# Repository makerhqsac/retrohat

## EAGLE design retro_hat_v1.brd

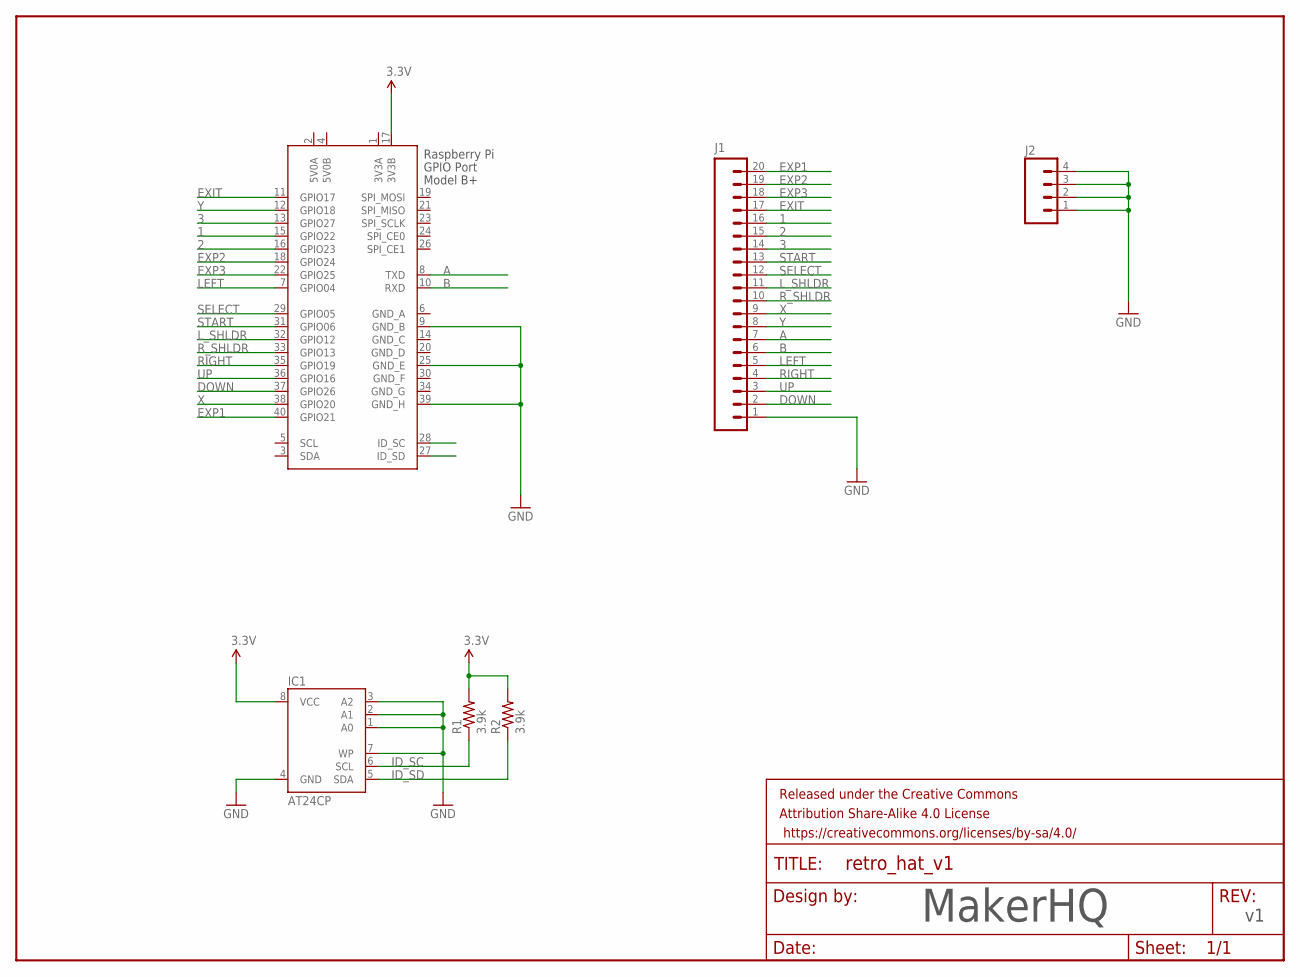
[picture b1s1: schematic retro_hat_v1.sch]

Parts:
FRAME1: FRAME-LETTERNO_PACKAGE; DUMMY
IC1: AT24CP; DIL08
J1: M20; 1X20
J2: M04PTH; 1X04
R1, R2: 3.9k; AXIAL-0.4
X1: RASPI_BOARD_B+#_HD; RASPI_BOARD_B+HAT_DF

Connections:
1: J1.16, X1.15 (GPIO22)
2: J1.15, X1.16 (GPIO23)
3: J1.14, X1.13 (GPIO27)
3.3V: IC1.8 (VCC), R1.P$2 (2), R2.P$2 (2), X1.17 (3V3B)
3V3A: X1.1 (3V3A)
5V0A: X1.2 (5V0A)
5V0B: X1.4 (5V0B)
A: J1.7, X1.8 (TXD)
B: J1.6, X1.10 (RXD)
DOWN: J1.2, X1.37 (GPIO26)
EXIT: J1.17, X1.11 (GPIO17)
EXP1: J1.20, X1.40 (GPIO21)
EXP2: J1.19, X1.18 (GPIO24)
EXP3: J1.18, X1.22 (GPIO25)
GND: IC1.1 (A0), IC1.2 (A1), IC1.3 (A2), IC1.4 (GND), IC1.7 (WP), J1.1, J2.1, J2.2, J2.3, J2.4, X1.9 (GND_B), X1.25 (GND_E), X1.39 (GND_H)
GND_A: X1.6 (GND_A)
GND_C: X1.14 (GND_C)
GND_D: X1.20 (GND_D)
GND_F: X1.30 (GND_F)
GND_G: X1.34 (GND_G)
ID_SC: IC1.6 (SCL), R1.P$1 (1), X1.28 (ID_SC)
ID_SD: IC1.5 (SDA), R2.P$1 (1), X1.27 (ID_SD)
LEFT: J1.5, X1.7 (GPIO04)
L_SHLDR: J1.11, X1.32 (GPIO12)
RIGHT: J1.4, X1.35 (GPIO19)
R_SHLDR: J1.10, X1.33 (GPIO13)
SELECT: J1.12, X1.29 (GPIO05)
START: J1.13, X1.31 (GPIO06)
UP: J1.3, X1.36 (GPIO16)
X: J1.9, X1.38 (GPIO20)
Y: J1.8, X1.12 (GPIO18)

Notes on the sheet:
MakerHQ

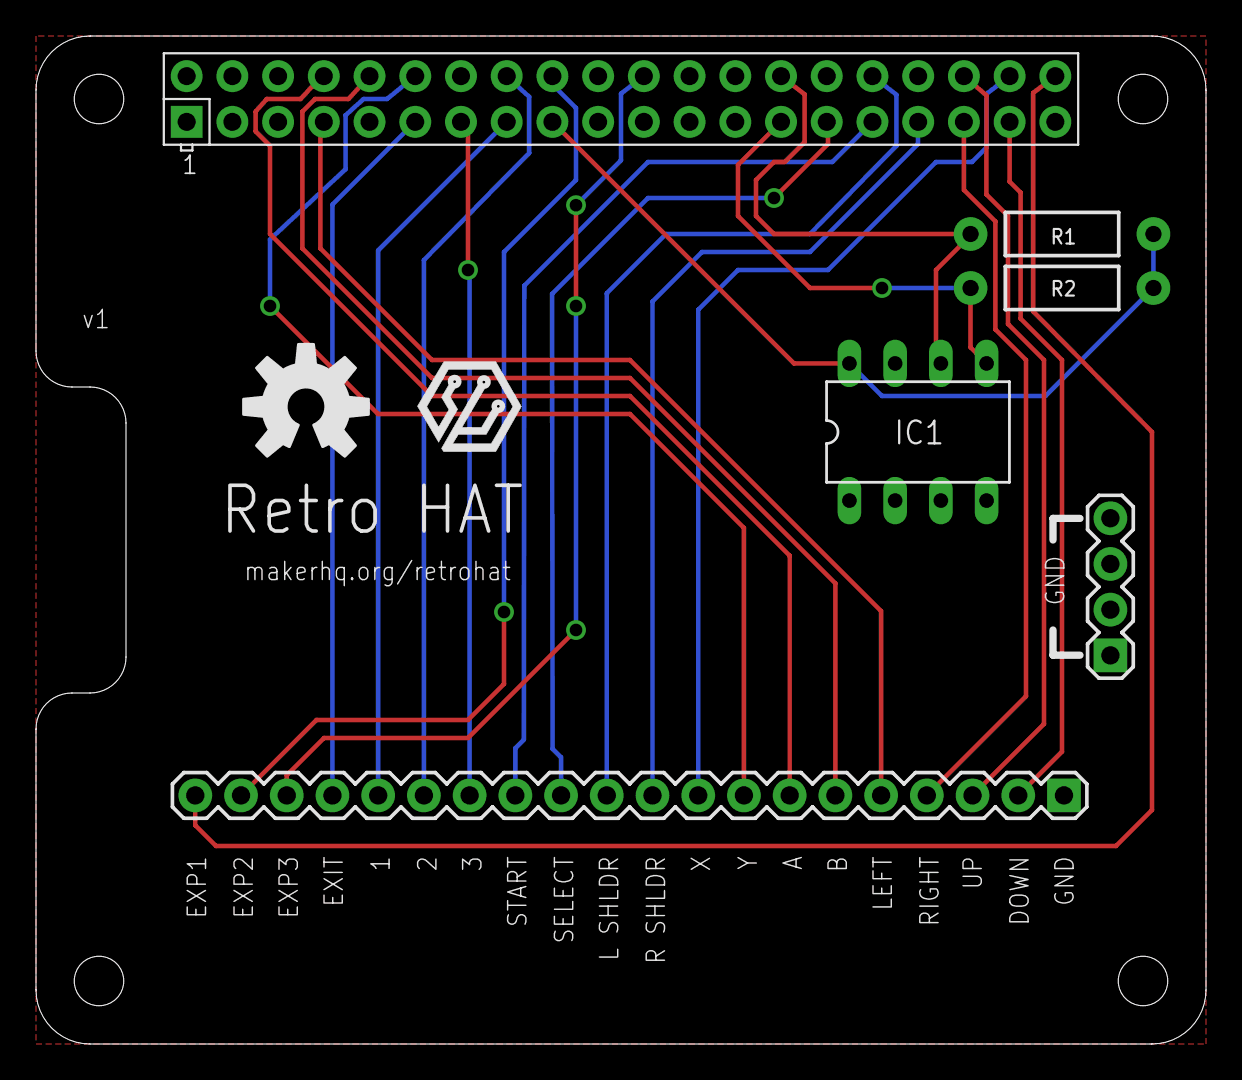
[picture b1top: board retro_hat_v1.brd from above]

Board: 2 copper layers, 65.0 x 56.0 mm, 9 parts (0 on the bottom side), 23 nets.

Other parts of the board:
U$1: MAKERHQ_LOGO_L
U$2: OSHW-LOGO-L

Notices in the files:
parts and their libraries:
SparkFun-Aesthetics: Licensing: Creative Commons ShareAlike 4.0 International - https://creativecommons.org/licenses/by-sa/4.0
SparkFun-Aesthetics: Released under the Creative Commons Attribution Share-Alike 4.0 License
SparkFun-Aesthetics: https://creativecommons.org/licenses/by-sa/4.0
